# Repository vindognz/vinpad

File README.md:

# VinPad - A submission for HackClub's Highway

### Specifications

BOM: 
- 6x Cherry MX Switches
- 1x XIAO RP2040
- 6x Blank DSA Keycaps

### Files:
- KMK Firmware
- top.step
- bottom.step

Schematic            |  PCB         |   Case
:-------------------------:|:-------------------------:|:-------------------------:|
    |    |

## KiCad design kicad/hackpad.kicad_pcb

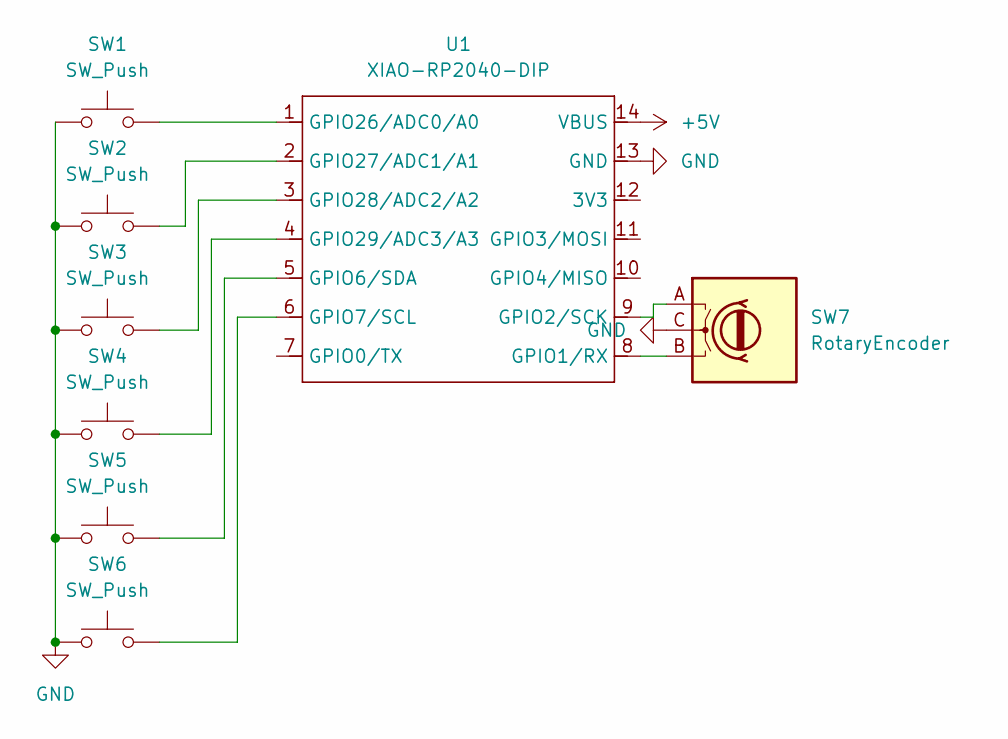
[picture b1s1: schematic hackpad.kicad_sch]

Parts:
SW1, SW2, SW3, SW4, SW5, SW6: SW_Push; SW_Cherry_MX_1.00u_PCB
SW7: RotaryEncoder; RotaryEncoder_Alps_EC11E-Switch_Vertical_H20mm_MountingHoles
U1: XIAO-RP2040-DIP

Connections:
+5V: U1.14 (VBUS)
GND: SW1.1, SW2.1, SW3.1, SW4.1, SW5.1, SW6.1, SW7.C, U1.13 (GND)
unnamed: SW7.B, U1.8 (GPIO1/RX)
unnamed: SW7.A, U1.9 (GPIO2/SCK)
unnamed: SW5.2, U1.5 (GPIO6/SDA)
unnamed: SW6.2, U1.6 (GPIO7/SCL)
unnamed: SW1.2, U1.1 (GPIO26/ADC0/A0)
unnamed: SW2.2, U1.2 (GPIO27/ADC1/A1)
unnamed: SW3.2, U1.3 (GPIO28/ADC2/A2)
unnamed: SW4.2, U1.4 (GPIO29/ADC3/A3)

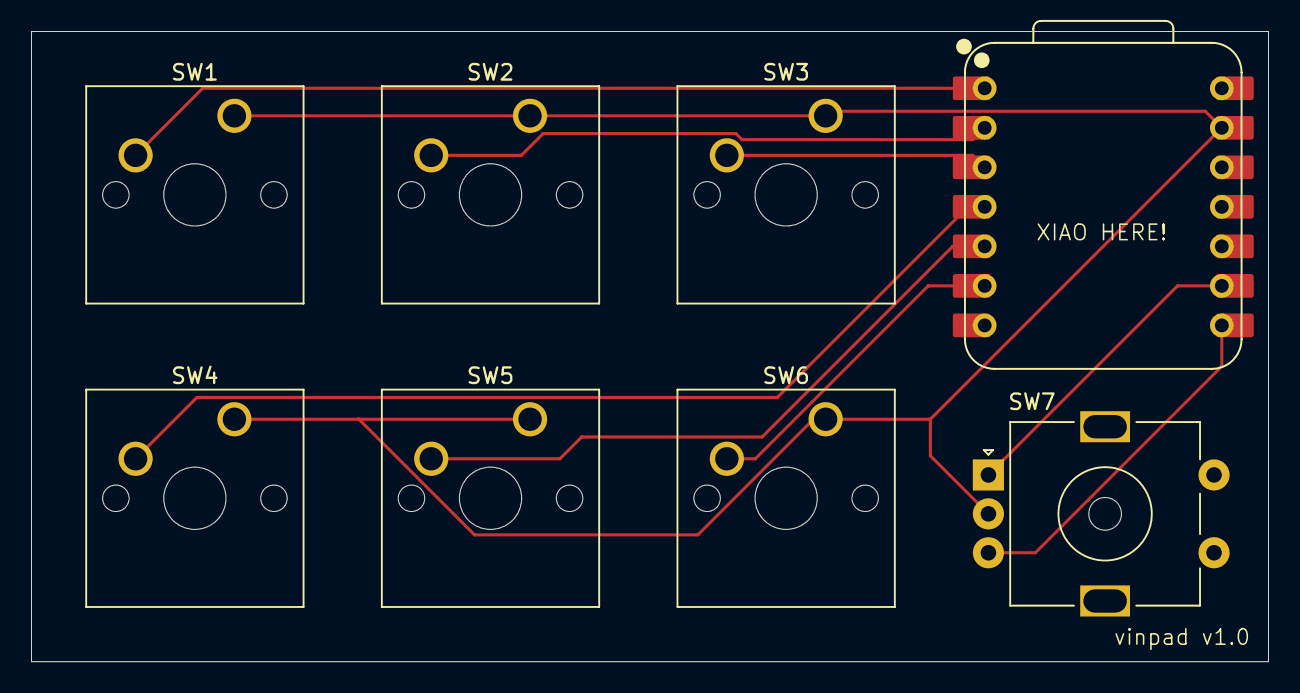
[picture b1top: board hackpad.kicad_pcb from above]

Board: 2 copper layers, 79.5 x 40.5 mm, 8 parts (0 on the bottom side), 9 nets.

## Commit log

2025-07-23 schematic and pcb pictures
2025-07-23 prepared setup for flashing, added actual firmware code
2025-07-23 added instructions for what to do when i get the hardware
2025-07-25 added final models
2025-07-25 organizing
2025-07-26 prettyy README
2025-07-26 case.png
2025-07-26 maybe final
